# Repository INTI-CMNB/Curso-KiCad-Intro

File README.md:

# Curso-KiCad-Intro
Curso introductorio al uso de KiCad, con modalidad taller,  armado a solicitud del proyecto CIAA

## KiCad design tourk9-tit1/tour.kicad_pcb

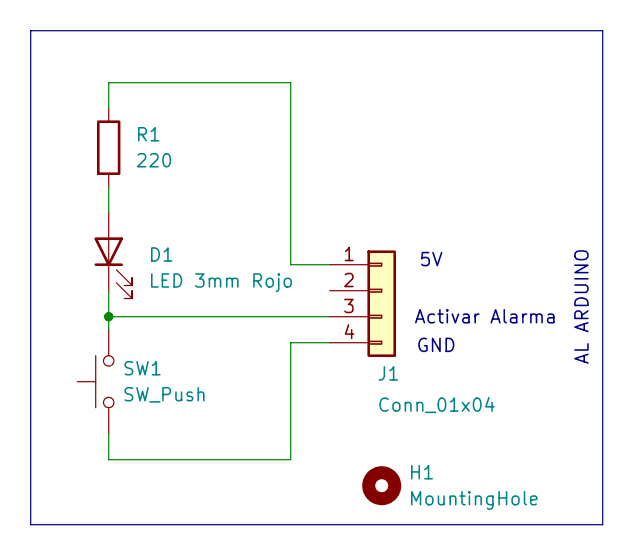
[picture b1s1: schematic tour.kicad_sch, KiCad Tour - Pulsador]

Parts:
D1: LED 3mm Rojo; LED_D3.0mm
H1: MountingHole; MountingHole_2.2mm_M2
J1: Conn_01x04; PinHeader_1x04_P2.54mm_Vertical
R1: 220; R_Axial_DIN0204_L3.6mm_D1.6mm_P7.62mm_Horizontal
SW1: SW_Push; SW_PUSH_6mm

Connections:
unnamed: D1.2 (A), R1.2
unnamed: D1.1 (K), J1.3, SW1.2
unnamed: J1.1, R1.1
unnamed: J1.4, SW1.1

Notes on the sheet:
Activar Alarma
AL ARDUINO
GND

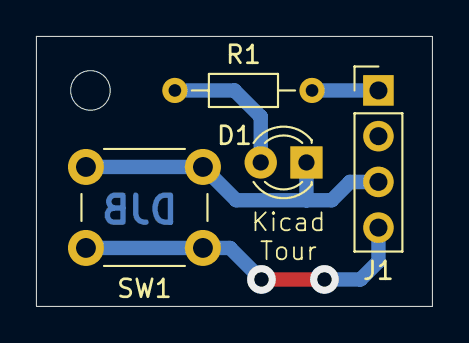
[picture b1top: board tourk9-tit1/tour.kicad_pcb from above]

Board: 2 copper layers, 22.0 x 15.0 mm, 5 parts (0 on the bottom side), 4 nets.

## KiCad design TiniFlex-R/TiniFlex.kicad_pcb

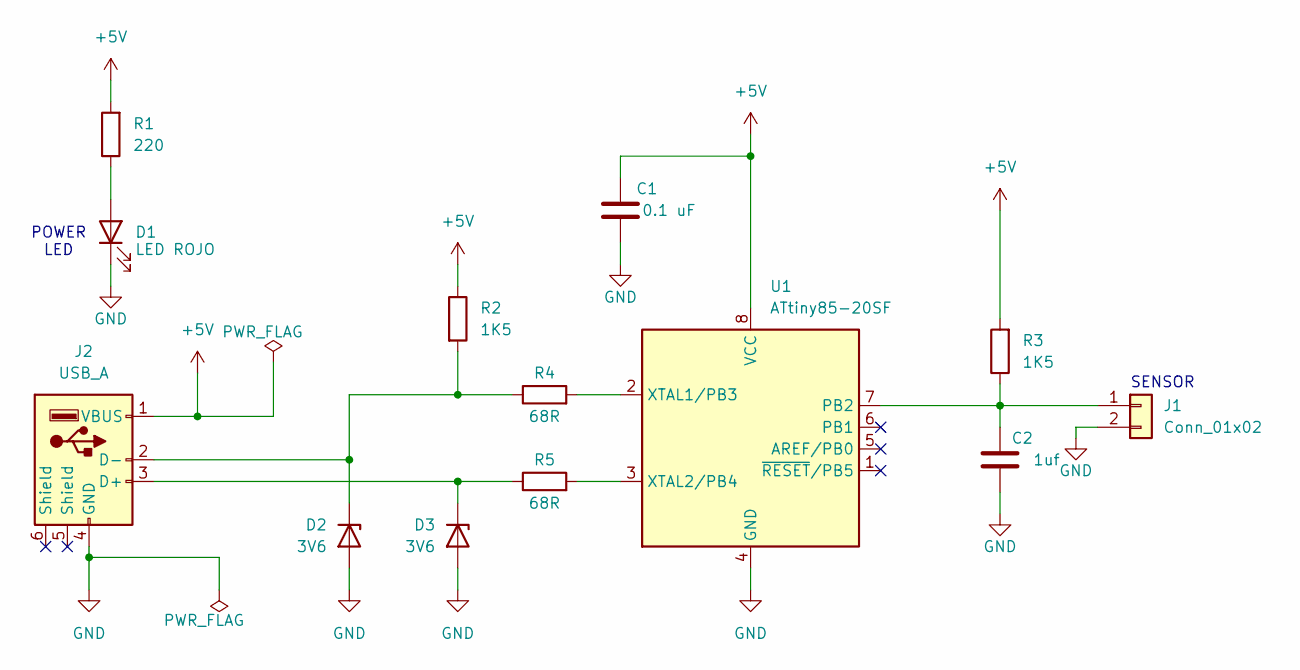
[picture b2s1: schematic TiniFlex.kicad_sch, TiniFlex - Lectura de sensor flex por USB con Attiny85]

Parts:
C1: 0.1 uF; C_0805_2012Metric_Pad1.18x1.45mm_HandSolder; Digikey# 399-C0805C104K5RACTUDKR-ND
C2: 1uf; C_0805_2012Metric_Pad1.18x1.45mm_HandSolder; Digikey# 490-10495-6-ND
D1: LED ROJO; LED_0805_2012Metric_Pad1.15x1.40mm_HandSolder; Digikey# 732-4985-6-ND
D2, D3: 3V6; D_SOD-123; Digikey# MMSZ4685T1GOSDKR-ND
J1: Conn_01x02; PinSocket_1x02_P2.54mm_Horizontal; Digikey# S5438-ND
J2: USB_A; USB_A_CNCTech_1001-011-01101_Horizontal; Digikey# 2057-USB-AP-S-RA-ND
R1: 220; R_0805_2012Metric_Pad1.20x1.40mm_HandSolder; Digikey# 311-220ARDKR-ND
R2, R3: 1K5; R_0805_2012Metric_Pad1.20x1.40mm_HandSolder; Digikey# 311-1.5KARDKR-ND
R4, R5: 68R; R_0805_2012Metric_Pad1.20x1.40mm_HandSolder; Digikey# 541-66.5CDKR-ND
U1: ATtiny85-20SF; SOIC-8W_5.3x5.3mm_P1.27mm; Digikey# ATTINY85-20SF-ND

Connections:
+5V: C1.1, J2.1 (VBUS), R1.2, R2.1, R3.2, U1.8 (VCC)
GND: C1.2, C2.2, D1.1 (K), D2.2 (A), D3.2 (A), J1.2, J2.4 (GND), U1.4 (GND)
unnamed: D1.2 (A), R1.1
unnamed: D2.1 (K), J2.2 (D-), R2.2, R4.1
unnamed: D3.1 (K), J2.3 (D+), R5.1
unnamed: C2.1, J1.1, R3.1, U1.7 (PB2)
unnamed: R4.2, U1.2 (XTAL1/PB3)
unnamed: R5.2, U1.3 (XTAL2/PB4)

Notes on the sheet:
SENSOR
POWER LED

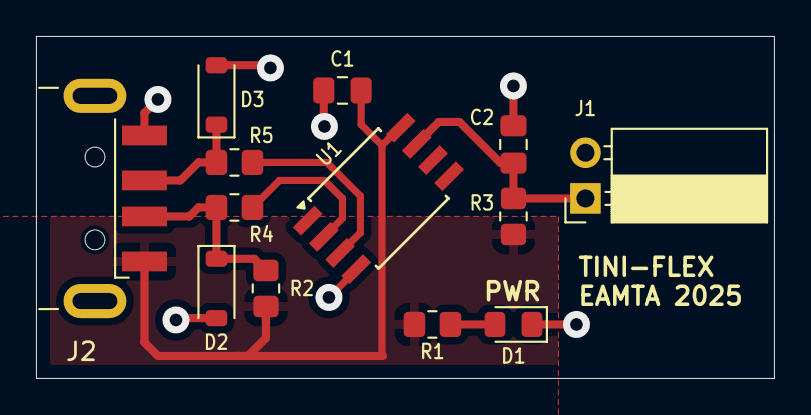
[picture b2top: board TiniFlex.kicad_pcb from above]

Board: 2 copper layers, 41.0 x 19.0 mm, 13 parts (0 on the bottom side), 8 nets.

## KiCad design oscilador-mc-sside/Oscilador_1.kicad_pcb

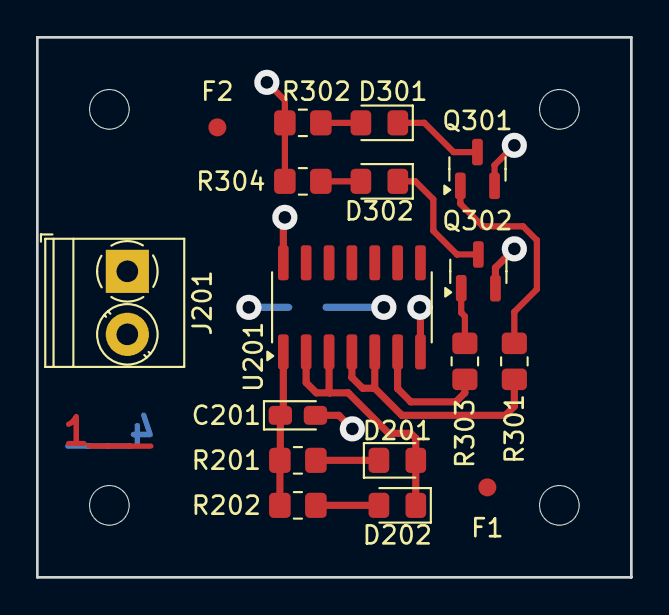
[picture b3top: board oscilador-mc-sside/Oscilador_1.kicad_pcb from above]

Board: 4 copper layers, 33.0 x 30.0 mm, 22 parts (1 on the bottom side), 9 nets.

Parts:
C201: 1uF; CP_EIA-2012-12_Kemet-R_Pad1.30x1.05mm_HandSolder
C202: 0.1u; C_0805_2012Metric_Pad1.18x1.45mm_HandSolder
D201, D202: 1N4148; D_0805_2012Metric_Pad1.15x1.40mm_HandSolder
D301: LED ROJO; LED_0805_2012Metric_Pad1.15x1.40mm_HandSolder
D302: LED VERDE; LED_0805_2012Metric_Pad1.15x1.40mm_HandSolder
F1, F2: Fiducial; Fiducial_1mm_Mask2mm
J201: Conn_01x02; TerminalBlock_Phoenix_PT-1,5-2-3.5-H_1x02_P3.50mm_Horizontal
MK101, MK102, MK103, MK104: Mounting_Hole; MountingHole_2.2mm_M2
Q301, Q302: BC846; SOT-23
R201: 100k; R_0805_2012Metric_Pad1.20x1.40mm_HandSolder
R202: 180k; R_0805_2012Metric_Pad1.20x1.40mm_HandSolder
R301, R303: 2k2; R_0805_2012Metric_Pad1.20x1.40mm_HandSolder
R302, R304: 470R; R_0805_2012Metric_Pad1.20x1.40mm_HandSolder
U201: 40106; SOIC-14_3.9x8.7mm_P1.27mm

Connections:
+5V: C202.1, J201.1, R302.1, R304.1, U201.14 (VDD)
/Leds/LED1: R301.2, U201.4, U201.5
/Leds/LED2: R303.2, U201.6
GND: C201.2, C202.2, J201.2, Q301.2 (E), Q302.2 (E), U201.7 (VSS)
unnamed: D201.2 (A), D202.1 (K), U201.2, U201.3
unnamed: D301.1 (K), Q301.3 (C)
unnamed: D302.1 (K), Q302.3 (C)
unnamed: Q301.1 (B), R301.1
unnamed: Q302.1 (B), R303.1

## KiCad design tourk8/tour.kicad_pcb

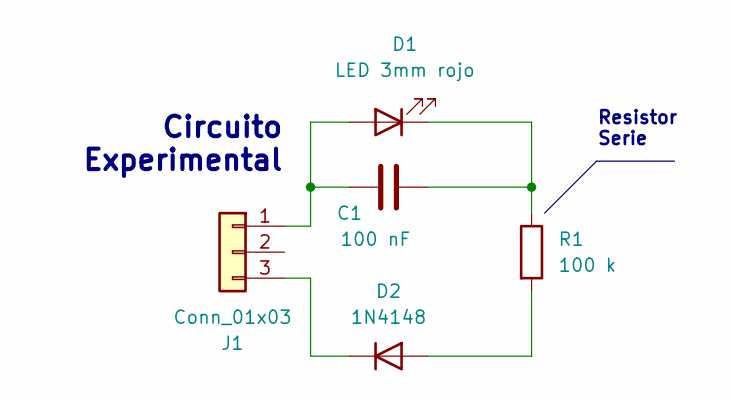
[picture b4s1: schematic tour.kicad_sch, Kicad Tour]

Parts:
C1: 100 nF; C_Disc_D4.3mm_W1.9mm_P5.00mm
D1: LED 3mm rojo; LED_D3.0mm
D2: 1N4148; D_DO-34_SOD68_P7.62mm_Horizontal
J1: Conn_01x03; PinHeader_1x03_P2.54mm_Vertical
R1: 100 k; R_Axial_DIN0207_L6.3mm_D2.5mm_P10.16mm_Horizontal

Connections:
unnamed: C1.1, D1.2 (A), J1.1
unnamed: C1.2, D1.1 (K), R1.1
unnamed: D2.2 (A), R1.2
unnamed: D2.1 (K), J1.3

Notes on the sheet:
Circuito Experimental
Resistor Serie

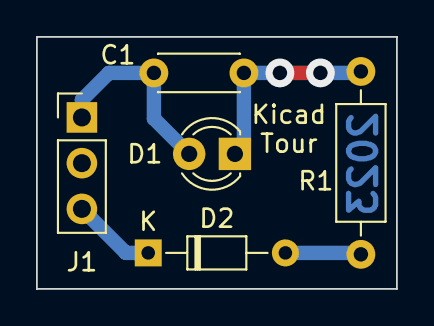
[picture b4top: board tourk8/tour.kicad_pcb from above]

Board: 2 copper layers, 20.0 x 14.0 mm, 5 parts (0 on the bottom side), 4 nets.

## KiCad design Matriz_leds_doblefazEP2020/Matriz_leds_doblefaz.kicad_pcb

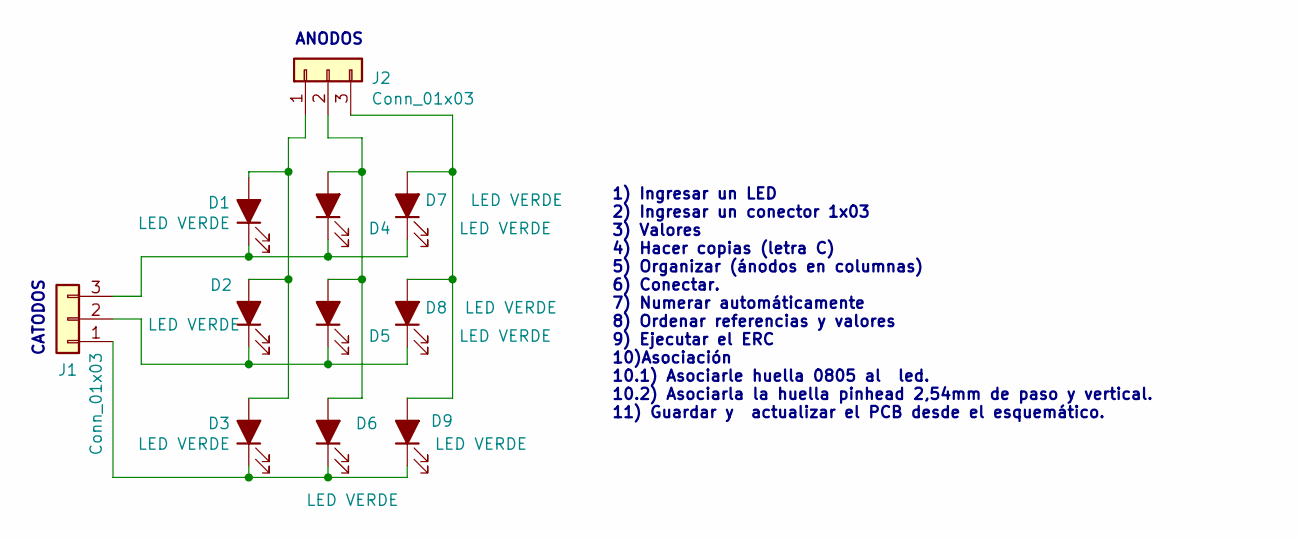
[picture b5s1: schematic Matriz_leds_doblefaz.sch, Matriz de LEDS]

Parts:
D1, D2, D3, D4, D5, D6, D7, D8, D9: LED VERDE; LED_0805_2012Metric_Castellated
J1, J2: Conn_01x03; PinHeader_1x03_P2.54mm_Vertical

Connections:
unnamed: D1.1 (K), D4.1 (K), D7.1 (K), J1.3
unnamed: D1.2 (A), D2.2 (A), D3.2 (A), J2.1
unnamed: D2.1 (K), D5.1 (K), D8.1 (K), J1.2
unnamed: D3.1 (K), D6.1 (K), D9.1 (K), J1.1
unnamed: D4.2 (A), D5.2 (A), D6.2 (A), J2.2
unnamed: D7.2 (A), D8.2 (A), D9.2 (A), J2.3

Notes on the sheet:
ANODOS
CATODOS
1) Ingresar un LED 2) Ingresar un conector 1x03 3) Valores 4) Hacer copias (letra C) 5) Organizar (ánodos en columnas) 6) Conectar. 7) Numerar automáticamente 8) Ordenar referencias y valores 9) Ejecutar el ERC 10)Asociación 10.1) Asociarle huella 0805 al led. 10.2) Asociarla la huella pinhead 2,54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

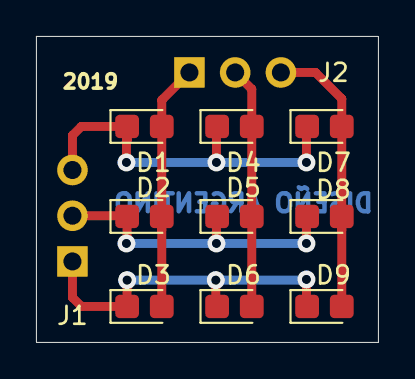
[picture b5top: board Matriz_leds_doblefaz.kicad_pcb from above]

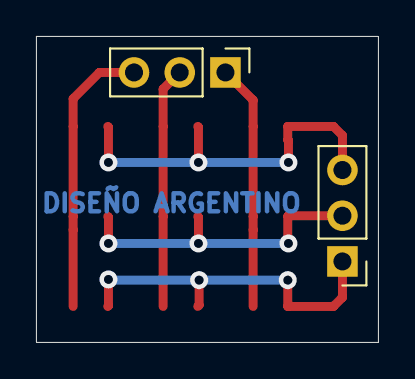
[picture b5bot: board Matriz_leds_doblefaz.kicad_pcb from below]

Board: 2 copper layers, 19.0 x 17.0 mm, 11 parts (2 on the bottom side), 6 nets.

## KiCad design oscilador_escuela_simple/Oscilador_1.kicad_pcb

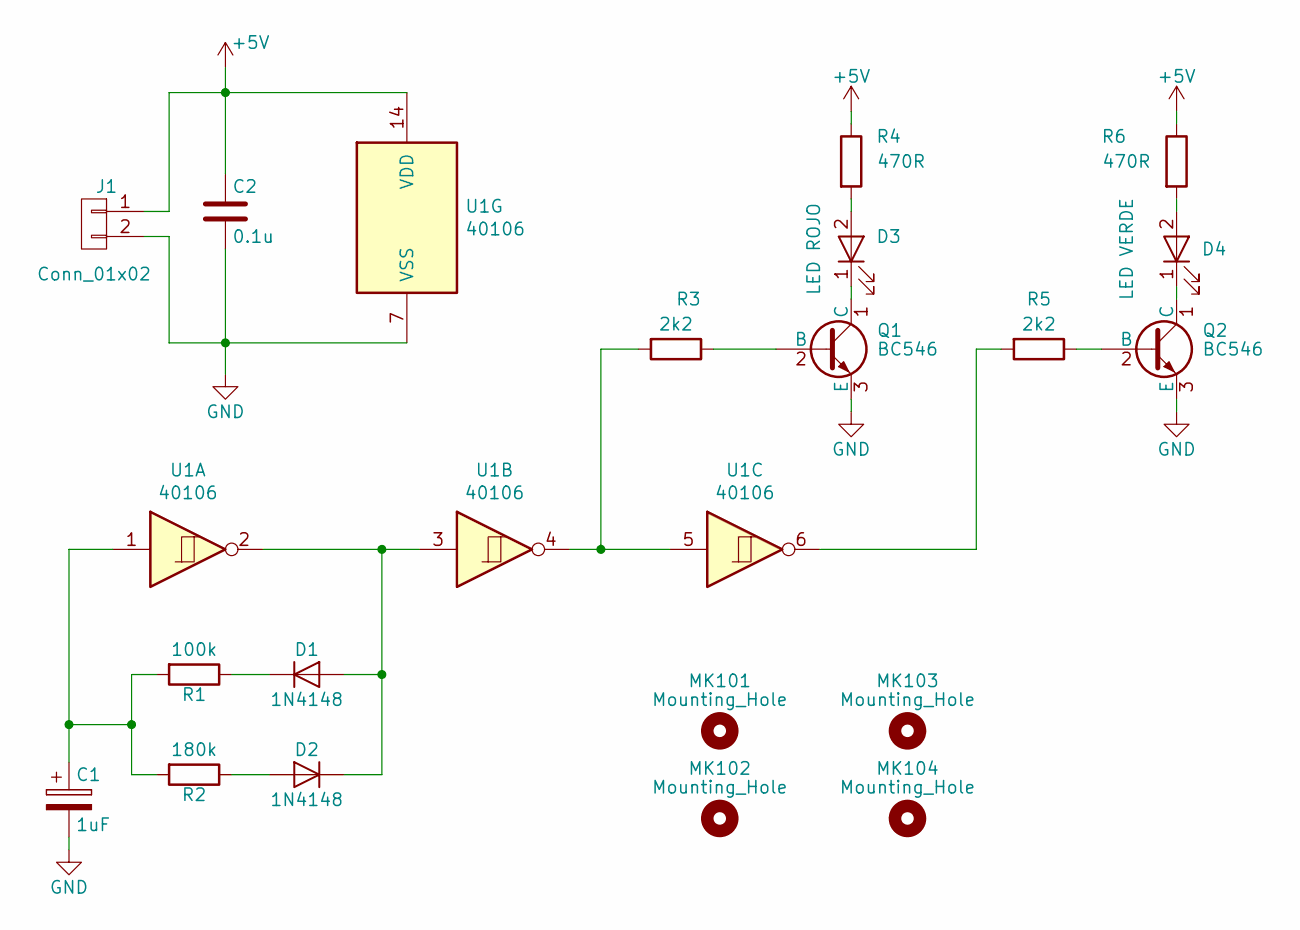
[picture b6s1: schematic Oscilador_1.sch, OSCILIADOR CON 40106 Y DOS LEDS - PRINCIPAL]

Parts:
C1: 1uF; CP_Radial_D5.0mm_P2.50mm
C2: 0.1u; C_Disc_D5.0mm_W2.5mm_P2.50mm
D1, D2: 1N4148; D_DO-41_SOD81_P10.16mm_Horizontal
D3: LED ROJO; LED_D3.0mm
D4: LED VERDE; LED_D3.0mm
J1: Conn_01x02; TerminalBlock_bornier-2_P5.08mm
MK101, MK102, MK103, MK104: Mounting_Hole; MountingHole_3.2mm_M3
Q1, Q2: BC546; TO-92_Molded_Wide_Oval
R1: 100k; R_Axial_DIN0207_L6.3mm_D2.5mm_P10.16mm_Horizontal
R2: 180k; R_Axial_DIN0207_L6.3mm_D2.5mm_P10.16mm_Horizontal
R3, R5: 2k2; R_Axial_DIN0207_L6.3mm_D2.5mm_P10.16mm_Horizontal
R4, R6: 470R; R_Axial_DIN0207_L6.3mm_D2.5mm_P10.16mm_Horizontal
U1: 40106; DIP-14_W7.62mm_LongPads

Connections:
+5V: C2.1, J1.1, R4.1, R6.1, U1.14 (VDD)
GND: C1.2, C2.2, J1.2, Q1.3 (E), Q2.3 (E), U1.7 (VSS)
unnamed: C1.1, R1.2, R2.2, U1.1
unnamed: D1.1 (K), R1.1
unnamed: D1.2 (A), D2.1 (K), U1.2, U1.3
unnamed: D2.2 (A), R2.1
unnamed: D3.1 (K), Q1.1 (C)
unnamed: D3.2 (A), R4.2
unnamed: D4.1 (K), Q2.1 (C)
unnamed: D4.2 (A), R6.2
unnamed: Q1.2 (B), R3.1
unnamed: Q2.2 (B), R5.1
unnamed: R3.2, U1.4, U1.5
unnamed: R5.2, U1.6

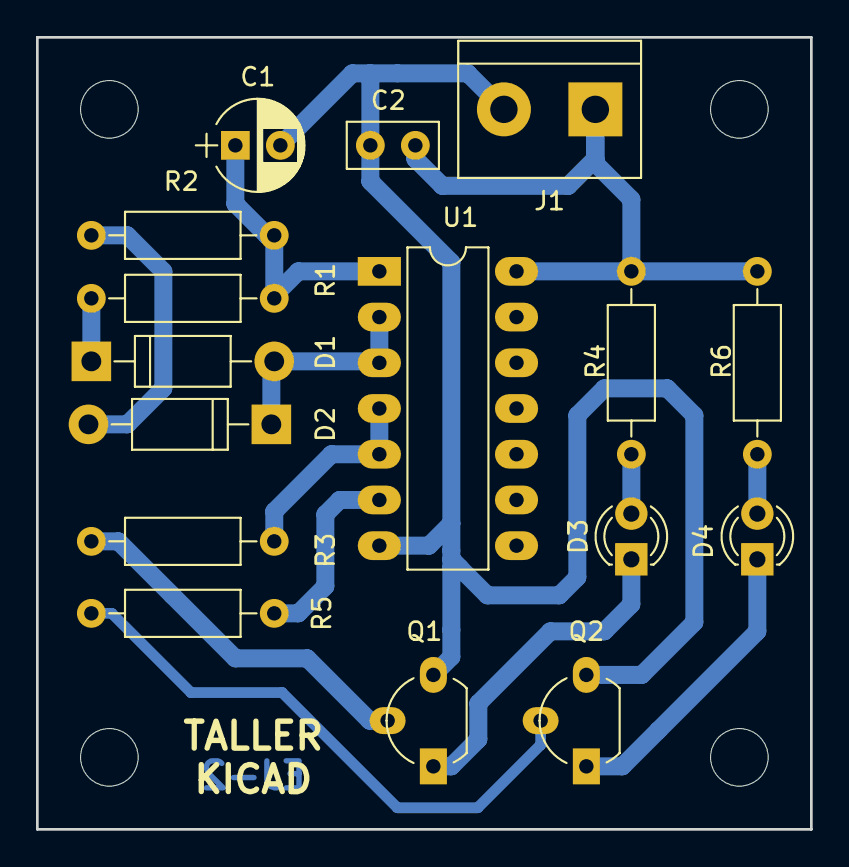
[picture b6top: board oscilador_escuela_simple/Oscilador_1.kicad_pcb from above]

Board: 2 copper layers, 43.0 x 44.0 mm, 20 parts (0 on the bottom side), 14 nets.

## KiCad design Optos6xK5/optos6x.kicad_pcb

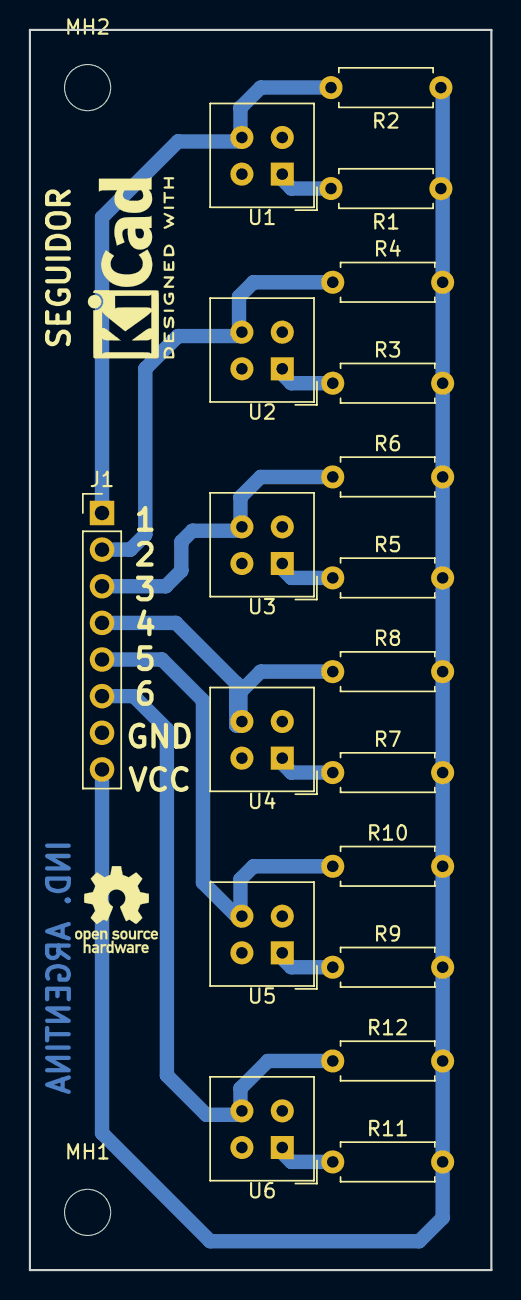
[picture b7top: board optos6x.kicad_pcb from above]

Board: 2 copper layers, 32.0 x 86.0 mm, 22 parts (0 on the bottom side), 14 nets.

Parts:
J1: Conn_01x08; PinHeader_1x08_P2.54mm_Vertical
LOGO1: Logo_Open_Hardware_Small; OSHW-Logo_5.7x6mm_SilkScreen
MH1, MH2: MountingHole; MountingHole_3.2mm_M3
R1, R3, R5, R7, R9, R11: 220; R_Axial_DIN0207_L6.3mm_D2.5mm_P7.62mm_Horizontal
R2, R4, R6, R8, R10, R12: 4K7; R_Axial_DIN0207_L6.3mm_D2.5mm_P7.62mm_Horizontal
U1, U2, U3, U4, U5, U6: CNY70; Vishay_CNY70

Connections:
GND: J1.7, U1.2, U1.4, U2.2, U2.4, U3.2, U3.4, U4.2, U4.4, U5.2, U5.4, U6.2, U6.4
unnamed: J1.1, R2.2, U1.3
unnamed: J1.2, R4.1, U2.3
unnamed: J1.3, R6.1, U3.3
unnamed: J1.4, R8.1, U4.3
unnamed: J1.5, R10.1, U5.3
unnamed: J1.6, R12.1, U6.3
unnamed: R1.2, U1.1
unnamed: R3.1, U2.1
unnamed: R5.1, U3.1
unnamed: R7.1, U4.1
unnamed: R9.1, U5.1
unnamed: R11.1, U6.1
VCC: J1.8, R1.1, R2.1, R3.2, R4.2, R5.2, R6.2, R7.2, R8.2, R9.2, R10.2, R11.2, R12.2

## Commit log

2015-11-03 Creo un proyecto nuevo.
2015-11-03 Completo rótulo y agrego símbolos.
2015-11-03 Agregado de asociación de footprints en el esquemático.
2015-11-04 Emprolijo esquemático.
2015-11-16 Agregado el PCB y varios archivos intermedios. Tambien .ib y 3ds.
2015-11-17 Agregado de la R2.
2015-11-17 Agrego reportes varios: gerbers, drill, etc.
2015-11-17 Renombro directorio a Ejercicio1.
2015-11-18 Corrijo ruta 3d.
2015-11-19 Agrego un primer borrador del ejercicio2.
2015-11-23 Agrego bus al esquemático. Quito resistor adicional.
2015-11-23 Muevo los scripts para el BOM.
2015-11-24 Borro scripts BOM innecesarios.
2015-11-24 Cambio numeración (OJO:PCB ROTO), cambio plugin BOM, quito R de VCC.
2015-11-24 Agrego el script para el bom.
2015-11-24 Ajustes en las referencias del pcb para reflejar cambios en el esquemático.
2015-11-25 Agregado de zonas de cobre (Igual hay que rehacer con plano de tierra).
2015-11-26 Versión del Ejercicio2 con CAN.
2015-11-26 Ejercicio 2+CAN, footprints agregados.
2015-11-26 Ejercicio 2, agregados los modelos 3D.
2015-11-26 Ejercicio 2. Corregida serigrafía Conn_Poncho.
2015-11-26 Agrego modelos 3D de capacitores y resistores.
2015-11-26 Borro y agrego algunos footprints.
2015-11-26 Agregado logos y plantillas al ejercicio 2.
2015-11-26 Completo rótulo y agrego leyendas al PCB.
2015-11-26 Agrego archivos de licencia.
2015-11-26 Agregado de info de licencia en rótulos.
2015-11-26 Detalles visuales y agrgado de comentarios.
2015-11-26 Agregado de directorios de hojas de datos y gerber.
2015-11-27 Agregado BOM final en formato LibreOffice.
2015-11-27 Completos campos en el esquemático.
2015-11-27 Se borran los archivos .wings.
2015-11-27 Agregados de keepout, cutout areas y más textos en drawings.
2015-11-30 Agrego ejercicio de símbolo multiparte en el día 3.
2015-11-30 Agrego archivos gerber generados al ejercicio 2.
2016-05-18 Modifico campos de información en el esquemático para funcionar con Kicost.
2016-05-19 Agrego ejercicio de 4 capas para el CESE.
2016-05-29 Agrego el ejercicio 2 versión TH super simple para el curso de Ponchos.
2016-05-29 Detalles menores de rótulos.
2016-05-31 Agrego RS232 multipart al esquemático. Cambio nombres de líneas seriales.
2016-06-06 Agrego stackup al Ejercicio2cese.
2016-06-06 Esquemárico más compacto para entrar mejor en las presentaciones.
2016-06-06 Detalles del verificador de capas y limpio bibliotecas del esquemático.
2016-06-13 Correcciones en los campos de información para KiCost.
2016-06-13 Corrección campos del multiparte.
2016-06-13 Agrego BOM con Kicost.
2016-06-14 Quito permisos de ejecución a algunos archivos.
2016-06-14 Reparo asignación de footprint para U1.
2016-08-09 Agrego el ejercicio de Reles2x para el Workshop del SASE.
2016-08-09 Cambio nombres.
2016-08-09 Agrego hojas de datos y BOM con KiCost.
2016-08-09 Agrego campos para KiCost.
2016-08-09 Detalles al esquemático y al PCB.
2016-08-09 Reparo la vista 3D.
2016-08-11 Corrección de rutas en los .kicad_mod.
2016-08-16 Corrijo error de LED invertido por biblioteca device legqacy.
2016-10-18 Agrego ejercico Rele1x.
2016-10-19 Avances Poncho Rele1x.
2016-10-20 Mejoras al ejercicio Rele1x.
2016-10-23 Detalles en el PCB serigrafía, etc.
2016-10-23 Borro footprints que no se usan.
2016-10-23 Agrego power flag.
2017-07-01 Rele1x: Agrego texto CAPSE, emprolijo pistas, agrego cota, info para array de impresión. Agrego impresiones.
2017-10-30 Versión nueva del Ejercicio 1 de Kicad Tour.
2017-11-01 Agrego ejercicio optos.
2017-11-01 Correccion modelo 3d bornera de ejercicio 1.
2017-11-04 Agrego nombre a la serigrafía y detalles.
2018-06-28 Agrego gitignore del nuevo ejercicio TH.
2018-06-28 Agrego ejercicio oscilador simple faz, TH.
2018-07-09 Agrego huellas y modelos 3D al repo local.
2018-07-21 Corrijo rutas relativas de los modelos 3d.
2018-07-21 Huellas con rutas relativas a los modelos 3D.
2018-09-04 Agrego gitignore para tourk2.
2018-09-10 Agrego ejercicio de optos con Kicad 5.
2018-09-26 Agrego ejercicio oscilador multicapa.
2018-09-26 Agrego modelos 3d y huellas.
2018-09-28 Agrego cache
2018-09-28 Ejercicio terminado multicapa.
2018-09-28 Agrego verificador de capas.
2019-07-16 Agrego oscilador Escuela simple hoja.
2019-07-16 Agrego gitignore
2019-07-16 Agrego ejercicio de matriz de leds.
2019-07-16 Agrego vistas 3D al esquemático.
2019-09-02 Agrego modelos 3D del ejercio Tour k5.
2019-11-22 Agrego archivos para fabricar en el taller de electrónica.
2020-11-12 Agrego Ejercicio ExpoProyecto 2020.
2021-04-15 Detalles de grilla, agrego margen, agrego notas de stackup, Corrección errores de DRC por cerca.
2022-06-13 Agrego ejercicio Kicad Tour para la versión 6.0.
2022-06-14 Avances en el PCB.
2023-06-10 Agrego ejercicio de kicad tour para kicad 7.
2024-08-29 Agrego ejercicio Kicad Tour 8
2024-08-29 Corrijo .gitignore.
2024-09-02 Agrego ejercicio oscilador multicapa single side.
2024-09-02 Actualizo archivos .gitignore
2024-09-02 Detalles de configuración.
2024-09-02 Agrego ejercicio de powrflag.
2024-09-02 Detalles de kicad multicapa 2024.
2024-10-10 Agrego kicad tour k8 para asignatura TIT1.
2025-02-25 Agrego ejercicio de TiniFlex recortado.
2025-02-26 Giro el integrado de TiniFlex-R
2025-06-14 Agrego version kicad 9.
